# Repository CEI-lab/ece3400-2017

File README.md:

# ECE 3400 Intelligent Physical Systems

The main page can be found under ./docs/index.md

Place documents that are only of relevance to the TAs and the instructor in the root of the repository (e.g. To Do lists, treasure PCB design, etc.).

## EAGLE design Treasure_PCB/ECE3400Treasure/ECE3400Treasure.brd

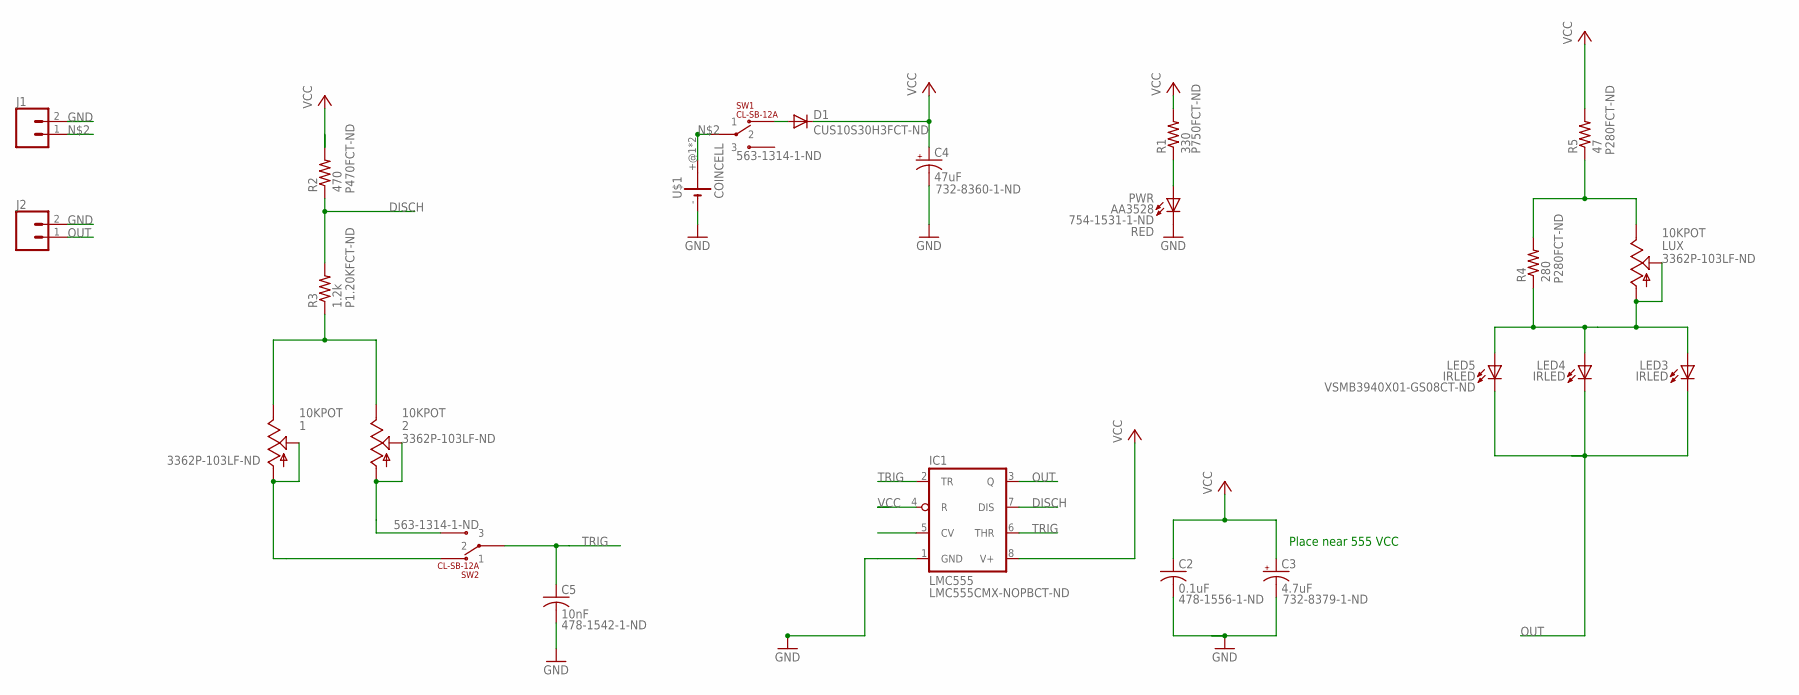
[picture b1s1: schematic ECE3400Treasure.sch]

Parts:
1, 2: 10KPOT; POT
C2: 0.1uF; C1206
C3: 4.7uF; UD-6,6X6,6
C4: 47uF; UD-6,6X6,6
C5: 10nF; C1206
D1: DIODE-SOD323-R; SOD323-R
IC1: LMC555; SO08
J1, J2: CONN_02; 1X02
LED3, LED4, LED5: IRLED; 2-SMD
LUX: 10KPOT; POT
PWR: AA3528; 2-PLCC
R1: 330; R1206
R2: 470; R1206
R3: 1.2k; R1206
R4: 280; R1206
R5: 47; R1206
SW1, SW2: CL-SB-12A
U$1: COINCELL

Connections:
DISCH: IC1.7 (DIS), R2.1, R3.2
GND: C2.2, C3.-, C4.-, C5.2, IC1.1 (GND), J1.2, J2.2, PWR.P$2 (C), U$1.-
unnamed: PWR.P$1 (A), R1.1
unnamed: J1.1, SW1.1 (2), U$1.+@1 (+), U$1.+@2 (+)
unnamed: D1.A, SW1.2 (1)
unnamed: 2.P$1 (A), 2.P$2 (S), SW2.3
unnamed: 1.P$1 (A), 1.P$2 (S), SW2.2 (1)
unnamed: 1.P$3 (E), 2.P$3 (E), R3.1
unnamed: LED3.P$1 (A), LED4.P$1 (A), LED5.P$1 (A), LUX.P$1 (A), LUX.P$2 (S), R4.1
unnamed: LUX.P$3 (E), R4.2, R5.1
OUT: IC1.3 (Q), J2.1, LED3.P$2 (C), LED4.P$2 (C), LED5.P$2 (C)
TRIG: C5.1, IC1.2 (TR), IC1.6 (THR), SW2.1 (2)
VCC: C2.1, C3.+, C4.+, D1.C, IC1.4 (R), IC1.8 (V+), R1.2, R2.2, R5.2

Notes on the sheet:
Place near 555 VCC

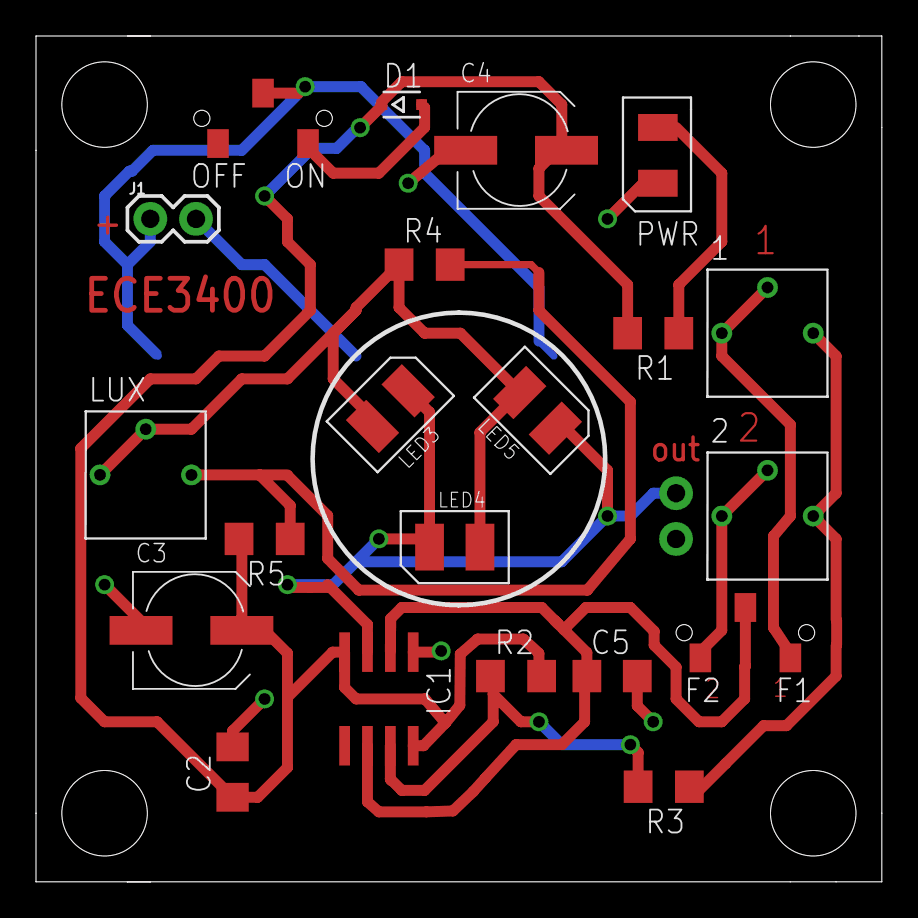
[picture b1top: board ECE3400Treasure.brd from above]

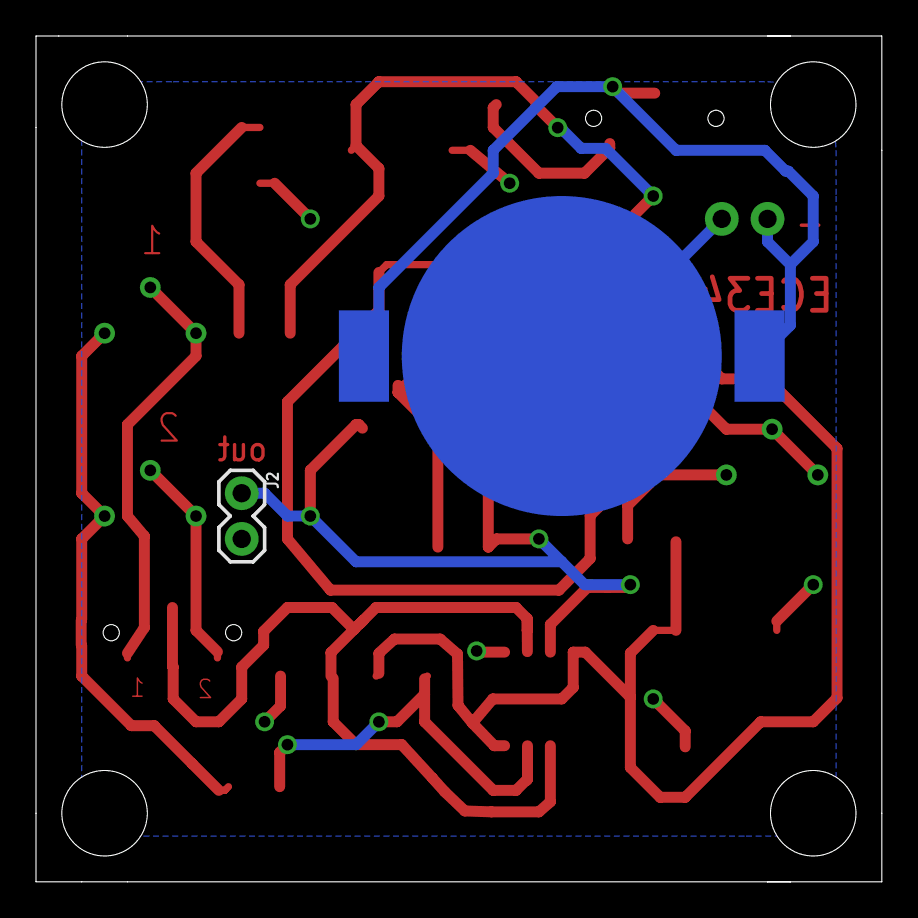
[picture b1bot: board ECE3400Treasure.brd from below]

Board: 2 copper layers, 47.0 x 47.0 mm, 23 parts (2 on the bottom side), 13 nets.

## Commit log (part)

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2017-08-14 Small spelling change
2017-08-15 Small spellng error
2017-08-15 Ryan description.
2017-08-15 Added additional descriptions
2017-08-15 Corrected spelling mistakes
2017-08-15 Spelling Errors/Small fixes
2017-08-15 More small changes
2017-08-16 Small spelling fixes
2017-08-16 Spelling correction
2017-08-17 Added wattage of laser cutter
2017-08-17 Lab 1 TA reference
2017-08-17 Added lab 2 to TA labs
2017-08-18 Changing Curran's e-mail
    His e-mail address is listed as mine lol
2017-08-18 Added TA labs 3 and 4
2017-08-18 Changes to TA labs 3 and 4
2017-08-18 Added more help to TA labs
2017-08-18 updated FPGA resources
2017-08-21 Curran picture
2017-08-26 Added new ball caster mounts and resistor values for VGA
2017-08-28 Update index.md
    I've been told by a fellow TA that this sounds pretentious...
2017-09-04 Set theme jekyll-theme-modernist
2017-09-08 Added link to Getting Started in lab 4
2017-09-12 lab 2 treasure clarifications
2017-09-15 Corrected IR phototransistor datasheet
2017-09-15 Added link to FFT library page and clarified which folder to add
2017-09-15 Fixed extra space
2017-09-16 New lecture slides
2017-09-19 Clarify amplification for treasure circuit
2017-09-22 new lab 3 template
2017-09-24 Added team zeta to websites
2017-09-26 update treasure placement in competition guidelines
2017-09-27 lab 3 lecture
2017-09-29 Added a space
2017-10-03 Added state machine example code link
2017-10-06 Updated milestone 3 grading
2017-10-06 Updated Lab 3 grading
2017-10-13 update formatting of milestone 3 grading
2017-10-13 Update milestone 3
2017-10-14 Added Bootstrap tutorial
2017-10-15 updated bootstrap tutorial
2017-10-15 Update bootstrap.md
    imbed = embed
2017-10-15 Rename colors_html.html to colors_html.md
2017-10-15 Rename colors_html.md to colors_html.html
2017-10-16 fix team identifier numbers
2017-10-31 added Arduino clarification to lab 3
2017-10-31 Updating Burn List and Suggested Components
2017-10-31 Update Burn List
2017-10-31 Update Component List
2017-11-01 Added component links
2017-11-01 Added info about importing components
2017-11-01 Added FPGA FAQ's
2017-11-01 Added another FAQ
2017-11-03 Created FAQ's file
2017-11-03 took out FAQ
2017-11-03 Rename FAQ's about Debugging to FPGA_FAQ.md
2017-11-06 treasure PCB updated
2017-11-08 Team evals
2017-11-08 Updated evaluation forms
2017-11-08 updated example forms
2017-11-08 Updated formatting in eval to render newlines on GitHub
2017-11-10 pcb modified
2018-04-08 Set theme jekyll-theme-dinky

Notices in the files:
parts and their libraries:
SparkFun-Connectors: Licensing: Creative Commons ShareAlike 4.0 International - https://creativecommons.org/licenses/by-sa/4.0
